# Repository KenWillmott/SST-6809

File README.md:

# SST-6809
MC6809 Single Board Computer

The SST is a stand alone MC6809 computer. It is inspired by the simple MC6809 SBC designed by Grant Searle:
http://searle.x10host.com/6809/Simple6809.html
and committed to a PCB design by Jeff Tranter:
http://jefftranter.blogspot.com/2019/01/a-6809-single-board-computer.html

It can be seen that what I call the Searle-Tranter design, has the following features:
- minimal ICs employed to make a useful stand alone system
- no PAL, GAL, or other programmable support logic ("glue") IC's, instead only standard 74xx MSI logic parts
- entirely through hole, DIP IC construction consistent with a vintage design. No surface mount components at all

The SST-6809 maintains the same overall approach, while adding some improvements and enhancements. Thus it is a "Super Searle Tranter" or SST. The fundamental features are:
- fairly granular address decoding, using only 4 74xx devices and one address latch for expanded memory
- full featured expansion bus, several expansion boards are already available
- separate UART and CPU clocks, allowing the MCU to run at the maximum 2.0MHz with the same 115200 baud communications
- 512kb NVRAM provides 56kb main and 456kb random access, battery backed up storage
- 32kb EEPROM jumper and software selectable in 4kb pages.
- option to use either USB adapter power, or 5V provided at screw connector terminals

The 10cm x 10cm form factor, including standard connector and mounting locations, create a "family" of boards that can interoperate in different ways. As a very minimal board, the SST does not support all of them, however its connector will support up to about 3 standard peripheral card in the M8 family, such as the M8 game board or the M8 6522/proto board. This can be accomplished using stacking connectors. The same boards may be used as vertically mounted cards on a bus - this configuration is a work in progress, however all the current cards could be used in that configuration instead (with a different connector installed).

The first PCB (V1.0) status was "assembled and testing". The EEPROM fails, a problem with the pin assignments was found.

The second and third PCB, V2.0 and V2.1, were completed. These intermediate versions do work, but V2.0 requires wire jumpers to replace a missing trace.

The current board version, V2.2, is fully operational and has some improvements such as selectable I/O memory address, and socket compatibility of 128/512k NVRAM IC's.

Detailed information can be found at:
https://exileinparadise.com/sst-6809:top
as well as the wiki:
https://github.com/KenWillmott/SST-6809/wiki

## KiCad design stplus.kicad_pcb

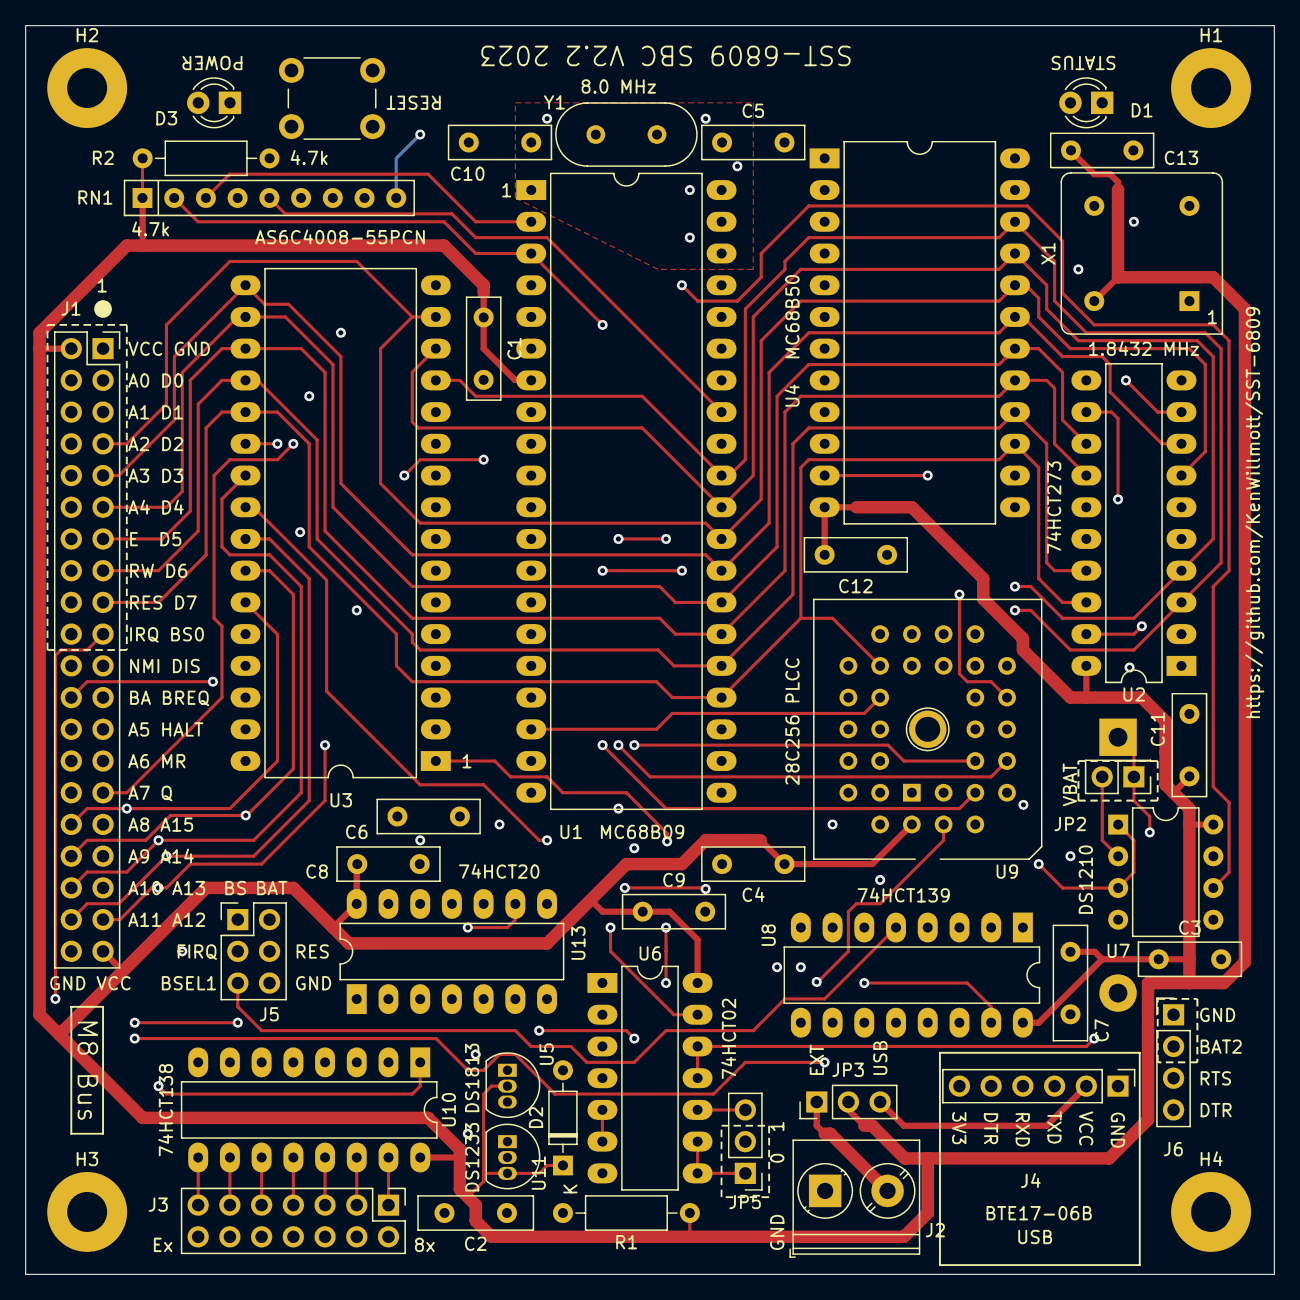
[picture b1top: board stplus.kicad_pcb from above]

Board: 4 copper layers, 100.0 x 100.0 mm, 48 parts (1 on the bottom side), 87 nets.

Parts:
BT1: 3.0V; BatteryHolder_Keystone_103_1x20mm
C1, C3, C4, C6, C8, C9, C11, C12, C13: 100nF; C_Disc_D8.0mm_W2.5mm_P5.00mm
C2: 10uF; C_Disc_D9.0mm_W2.5mm_P5.00mm
C5, C10: 20pF; C_Disc_D8.0mm_W2.5mm_P5.00mm
C7: 100nF; C_Disc_D9.0mm_W2.5mm_P5.00mm
D1: STAT; LED_D3.0mm
D2: 1N4148; D_DO-35_SOD27_P7.62mm_Horizontal
D3: PWR; LED_D3.0mm
H1, H2, H3, H4: MountingHole_Pad; MountingHole_3.2mm_M3_Pad
J1: Conn_02x20_Odd_Even; PinSocket_2x20_P2.54mm_Vertical
J2: Screw_Terminal_01x02; TerminalBlock_Phoenix_PT-1,5-2-5.0-H_1x02_P5.00mm_Horizontal
J3: Conn_02x07_Odd_Even; PinHeader_2x07_P2.54mm_Vertical
J4: Conn_01x06_Pin; PinHeader_1x06_P2.54mm_Vertical
J5: Conn_02x03_Odd_Even; PinHeader_2x03_P2.54mm_Vertical
J6: Conn_01x04_Pin; PinHeader_1x04_P2.54mm_Vertical
JP2: VBAT; PinHeader_2x01_P2.54mm_Vertical
JP3, JP5: Jumper_3_Bridged12; PinHeader_1x03_P2.54mm_Vertical
R1: 10k; R_Axial_DIN0207_L6.3mm_D2.5mm_P10.16mm_Horizontal
R2: 4.7k; R_Axial_DIN0207_L6.3mm_D2.5mm_P10.16mm_Horizontal
RN1: 4.7k; R_Array_SIP9
SW1: Reset; SW_PUSH_6mm_H5mm
U1: MC68B09; DIP-40_W15.24mm_LongPads
U2: 74HCT273; DIP-20_W7.62mm_LongPads
U3: AS6C4008-55PCN; DIP-32_W15.24mm_LongPads
U4: MC68B50; DIP-24_W15.24mm_LongPads
U5: DS1813; TO-92L_Inline
U6: 74HCT02; DIP-14_W7.62mm_LongPads
U7: DS1210; DIP-8_W7.62mm
U8: 74HCT139; DIP-16_W7.62mm_LongPads
U9: 28C256 PLCC; PLCC-32_THT-Socket
U10: 74HCT138; DIP-16_W7.62mm_LongPads
U11: DS1233; TO-92L_Inline
U13: 74HCT20; DIP-14_W7.62mm_LongPads
X1: CXO_DIP8; Oscillator_DIP-8
Y1: 8.0 MHz; Crystal_HC18-U_Vertical

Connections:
/A0: J1.4, U1.8 (A0), U3.12 (A0), U4.11 (RS), U9.11 (A0)
/A1: J1.6, U1.9 (A1), U3.11 (A1), U9.10 (A1)
/A2: J1.8, U1.10 (A2), U3.10 (A2), U9.9 (A2)
/A3: J1.10, U1.11 (A3), U3.9 (A3), U9.8 (A3)
/A4: J1.12, U1.12 (A4), U3.8 (A4), U9.7 (A4)
/A5: J1.26, U1.13 (A5), U3.7 (A5), U9.6 (A5)
/A6: J1.28, U1.14 (A6), U3.6 (A6), U9.5 (A6)
/A7: J1.30, U1.15 (A7), U3.5 (A7), U9.4 (A7)
/A8: J1.32, U1.16 (A8), U3.27 (A8), U4.10 (CS1), U9.29 (A8), U13.10
/A9: J1.34, U1.17 (A9), U3.26 (A9), U4.8 (CS0), U9.28 (A9), U13.12
/A10: J1.36, U1.18 (A10), U3.23 (A10), U8.2 (A0), U9.24 (A10)
/A11: J1.38, U1.19 (A11), U3.25 (A11), U8.3 (A1), U9.27 (A11)
/A12: J1.37, U1.20 (A12), U3.4 (A12), U10.1 (A0)
/A13: J1.35, U1.21 (A13), U3.28 (A13), U10.2 (A1)
/A14: J1.33, U1.22 (A14), U3.3 (A14), U10.3 (A2)
/A15: J1.31, U1.23 (A15), U6.2, U10.6 (E2)
/A15G: U3.31 (A15), U6.1
/D0: J1.3, U1.31 (D0), U2.3 (D0), U3.13 (DQ0), U4.22 (D0), U9.13 (D0)
/D1: J1.5, U1.30 (D1), U2.4 (D1), U3.14 (DQ1), U4.21 (D1), U9.14 (D1)
/D2: J1.7, U1.29 (D2), U2.7 (D2), U3.15 (DQ2), U4.20 (D2), U9.15 (D2)
/D3: J1.9, U1.28 (D3), U2.8 (D3), U3.17 (DQ3), U4.19 (D3), U9.18 (D3)
/D4: J1.11, U1.27 (D4), U2.13 (D4), U3.18 (DQ4), U4.18 (D4), U9.19 (D4)
/D5: J1.13, U1.26 (D5), U2.14 (D5), U3.19 (DQ5), U4.17 (D5), U9.20 (D5)
/D6: J1.15, U1.25 (D6), U2.17 (D6), U3.20 (DQ6), U4.16 (D6), U9.21 (D6)
/D7: J1.17, U1.24 (D7), U2.18 (D7), U3.21 (DQ7), U4.15 (D7), U9.22 (D7)
/DTR: J4.5, J6.4
/RTS: J6.3, U4.5 (~RTS)
/TXD: J4.4, U4.6 (Tx_Data)
/Z0: U2.2 (Q0), U6.3
/Z1: U2.5 (Q1), U3.2 (A16)
/Z2: U2.6 (Q2), U6.11, U6.12
/Z2*: U3.30 (A17), U6.13
/Z3: U2.9 (Q3), U3.1 (A18)
/decode/ACIASEL*: U4.9 (CS2), U8.6 (O2)
/decode/BSEL1*: J5.5, U8.5 (O1)
/decode/EERD*: U8.11 (O1), U9.25 (~OE)
/decode/EEWR*: U8.12 (O0), U9.31 (~WE)
/decode/LATSEL*: U2.11 (Cp), U13.8
/decode/NVBAT: BT1.1 (+), J5.2, JP2.1 (A)
/decode/NVCC: C6.1, U3.32 (VCC), U7.1 (VCCO), U7.3 (TOL)
/decode/NVCE*: U3.22 (CE#), U7.6 (~CEO)
/decode/NVRD*: U3.24 (OE#), U8.9 (O3)
/decode/NVWR*: U3.29 (WE#), U8.10 (O2)
/decode/Z6: JP5.1 (A), U2.16 (Q6), U6.8, U6.9
BA: J1.24, U1.6 (BA)
BREQ*: J1.23, RN1.5 (R4), U1.33 (~DMA/BREQ)
BS: J5.1, U1.5 (BS)
BSEL0*: J1.19, U8.4 (O0)
BT0: JP5.2 (C), U9.2 (A14)
DIS*: J1.21, RN1.4 (R3), U13.1
E: J1.14, U1.34 (E), U4.14 (E), U13.5, U13.9
FIRQ*: J5.3, RN1.8 (R7), U1.4 (~FIRQ)
GND: BT1.2 (-), C1.2, C2.2, C3.2, C4.2, C5.2, C6.2, C7.2, C8.2, C9.2, C10.2, C11.2, C12.2, C13.1, D3.1 (K), H1.1, H2.1, H3.1, H4.1, J1.1, J1.40, J2.1, J4.1, J5.6, J6.1, SW1.2, U1.1 (VSS), U2.10 (GND), U3.16 (VSS), U4.1 (VSS), U4.23 (~DCD), U4.24 (~CTS), U5.3 (GND), U6.7 (GND), U7.4 (GND), U7.5 (~CE), U8.8 (GND), U9.16 (GND), U9.23 (~CE), U10.4 (~E0), U10.5 (~E1), U10.8 (GND), U11.1 (GND), U13.7 (GND), X1.4 (GND)
HALT*: J1.25, RN1.6 (R5), U1.40 (~HALT)
IRQ*: J1.20, RN1.2 (R1), U1.3 (~IRQ), U4.7 (~IRQ)
MR: J1.27, RN1.7 (R6), U1.36 (MRDY)
NMI*: J1.22, RN1.3 (R2), U1.2 (~NMI)
unnamed: D1.2 (A), RN1.9 (R8)
unnamed: D3.2 (A), R2.2
unnamed: J2.2, JP3.1 (A)
unnamed: J3.1, U10.15 (~Y0)
unnamed: J3.3, U10.14 (~Y1)
unnamed: J3.5, U10.13 (~Y2)
unnamed: J3.7, U10.12 (~Y3)
unnamed: J3.9, U10.11 (~Y4)
unnamed: J3.2, J3.4, J3.6, J3.8, J3.10, J3.12, J3.14, U8.1 (E), U13.4
unnamed: J3.11, U10.10 (~Y5)
unnamed: J3.13, U10.9 (~Y6)
unnamed: J4.2, JP3.3 (B)
unnamed: JP2.2 (B), U7.2 (VBAT1)
unnamed: JP5.3 (B), U6.10
unnamed: C10.1, U1.38 (EXTAL), Y1.2
unnamed: C5.1, U1.39 (XTAL), Y1.1
unnamed: U4.3 (Rx_CLK), U4.4 (Tx_CLK), X1.5 (OUT)
unnamed: U6.5, U6.6, U8.7 (O3)
unnamed: U8.15 (E), U13.6
unnamed: U8.13 (A1), U10.7 (~Y7)
unnamed: U6.4, U13.13
Q: J1.29, U1.35 (Q)
RES*: C2.1, D2.2 (A), J1.18, J5.4, R1.2, SW1.1, U1.37 (~RESET), U2.1 (~Mr), U5.1 (~RESET), U11.2 (~RESET), U13.2
RXD: J4.3, U4.2 (Rx_Data)
R/W*: J1.16, U1.32 (R/~W), U4.13 (R/~W), U8.14 (A0)
VBAT2: J6.2, U7.7 (VBAT2)
VCC: C1.1, C3.1, C4.1, C7.1, C8.1, C9.1, C11.1, C12.1, C13.2, D2.1 (K), J1.2, J1.39, JP3.2 (C), R1.1, R2.1, RN1.1 (common), U1.7 (VCC), U2.20 (VCC), U4.12 (VCC), U5.2 (VCC), U6.14 (VCC), U7.8 (VCCI), U8.16 (VCC), U9.32 (VCC), U10.16 (VCC), U11.3 (VCC), U13.14 (VCC), X1.8 (Vcc)
Z4: U2.12 (Q4), U9.3 (A12)
Z5: U2.15 (Q5), U9.30 (A13)
Z7: D1.1 (K), U2.19 (Q7)

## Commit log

2023-10-08 beta schematic
2023-10-08 beta board image
2023-10-10 latest schematic
2025-05-18 Create foo
2025-05-18 microForth-6809
